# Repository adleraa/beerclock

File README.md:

# keyring_beerclock
A keyring portable device for meassuring time in the game of ölhäfv

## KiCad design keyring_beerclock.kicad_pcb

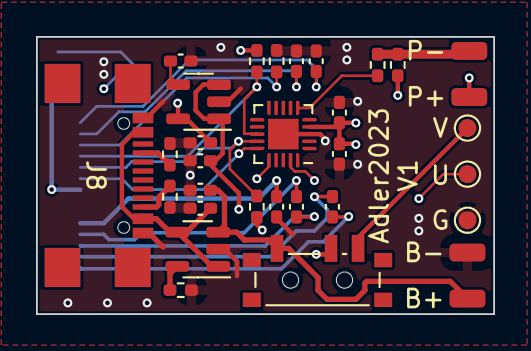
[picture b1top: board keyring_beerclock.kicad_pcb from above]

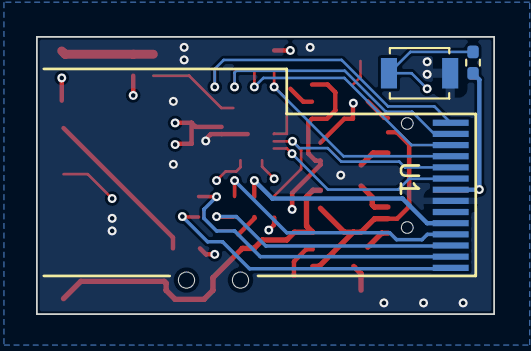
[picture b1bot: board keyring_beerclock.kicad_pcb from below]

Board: 4 copper layers, 25.4 x 15.4 mm, 35 parts (3 on the bottom side), 25 nets.

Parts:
C1, C2, C3, C4, C7, C9, C10, C11: 1uF; C_0402_1005Metric_Pad0.74x0.62mm_HandSolder
C5: 4.7uF; C_0402_1005Metric_Pad0.74x0.62mm_HandSolder
C6: 2.2uF; C_0402_1005Metric_Pad0.74x0.62mm_HandSolder
C8: 470pF; C_0402_1005Metric_Pad0.74x0.62mm_HandSolder
C12: 100n; C_0402_1005Metric_Pad0.74x0.62mm_HandSolder
J1: +BAT; SolderWirePad_1x01_SMD_1x2mm
J2: -BAT; SolderWirePad_1x01_SMD_1x2mm
J3: VCC; TestPoint_Pad_D1.0mm
J4: UDPI; TestPoint_Pad_D1.0mm
J5: GND; TestPoint_Pad_D1.0mm
J6: +PIEZO; SolderWirePad_1x01_SMD_1x2mm
J7: -PIEZO; SolderWirePad_1x01_SMD_1x2mm
J8: USB_C_Receptacle_USB2.0; SOFNG MC-311S USB-C
R1: 10K; R_0402_1005Metric_Pad0.72x0.64mm_HandSolder
R2: 330K; R_0402_1005Metric_Pad0.72x0.64mm_HandSolder
R3, R4, R7: 2K; R_0402_1005Metric_Pad0.72x0.64mm_HandSolder
R8: 100K; R_0402_1005Metric_Pad0.72x0.64mm_HandSolder
R9: 1M; R_0402_1005Metric_Pad0.72x0.64mm_HandSolder
R10, R11: 5K1; R_0402_1005Metric_Pad0.72x0.64mm_HandSolder
SW1: PWR_SEL; SW_SPDT_PCM12
SW3: BTN_RIGHT; SW_SPST_B3U-1000P
U1: SSD1306-14pin
U2: MCP73812T-420I-OT; SOT-23-5
U3: TC1014-3.3VCT713; SOT-23-5
U4: ATtiny1616-MNR; VQFN-20-1EP_3x3mm_P0.4mm_EP1.7x1.7mm

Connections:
+3V3: C10.1, C11.1, C12.1, J6.1, R3.1, R4.1, R7.1, R9.2, U1.8 (VDD), U3.5 (VOUT), U4.4 (VCC)
/-Piezo: J7.1, R8.2, R9.1
/BAT+: C7.1, J1.1, SW1.1 (A), U2.3 (VBAT)
/C1N: C2.2, U1.4 (C1N)
/C1P: C2.1, U1.3 (C1P)
/C2N: C1.2, U1.2 (C2N)
/C2P: C1.1, U1.1 (C2P)
/CC1: J8.A5 (CC1), R11.1
/CC2: J8.B5 (CC2), R10.1
/CRG_PROG: R1.1, U2.5 (PROG)
/IREF: R2.1, U1.12 (IREF)
/PWR_IN: C3.1, SW1.2 (B), U3.1 (VIN), U3.3 (~SHDN)
/VBAT: C9.1, U1.5 (VBAT)
/VBUS: C4.1, J8.A4 (VBUS), U2.1 (CEN), U2.4 (VDD)
/VCC_CAP: C6.1, U1.14 (VCC)
/VCOMM: C5.1, U1.13 (VCOMM)
/bypass: C8.1, U3.4 (Bypass)
BTN_RIGHT: R7.2, SW3.1, U4.16 (PC1)
GND: C3.2, C4.2, C5.2, C6.2, C7.2, C8.2, C9.2, C10.2, C11.2, C12.2, J2.1, J5.1, J8.A1 (GND), R1.2, R2.2, R10.2, R11.2, SW3.2, U1.7 (VSS), U2.2 (VSS), U3.2 (GND), U4.3 (GND), U4.21 (GND)
SCL: R3.2, U1.10 (SCL), U4.14 (PB0)
SDA: R4.2, U1.11 (SDA), U4.13 (PB1)
SENSE: R8.1, U4.6 (PA5)
UDPI: J4.1, U4.19 (~RESET/PA0)
VCC: J3.1, SW1.3 (C)
~RES: U1.9 (~RES), U4.15 (PC0)

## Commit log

2023-06-17 Starting fresh
2023-06-24 Finished layout, ready to order
2023-06-24 Ordered
